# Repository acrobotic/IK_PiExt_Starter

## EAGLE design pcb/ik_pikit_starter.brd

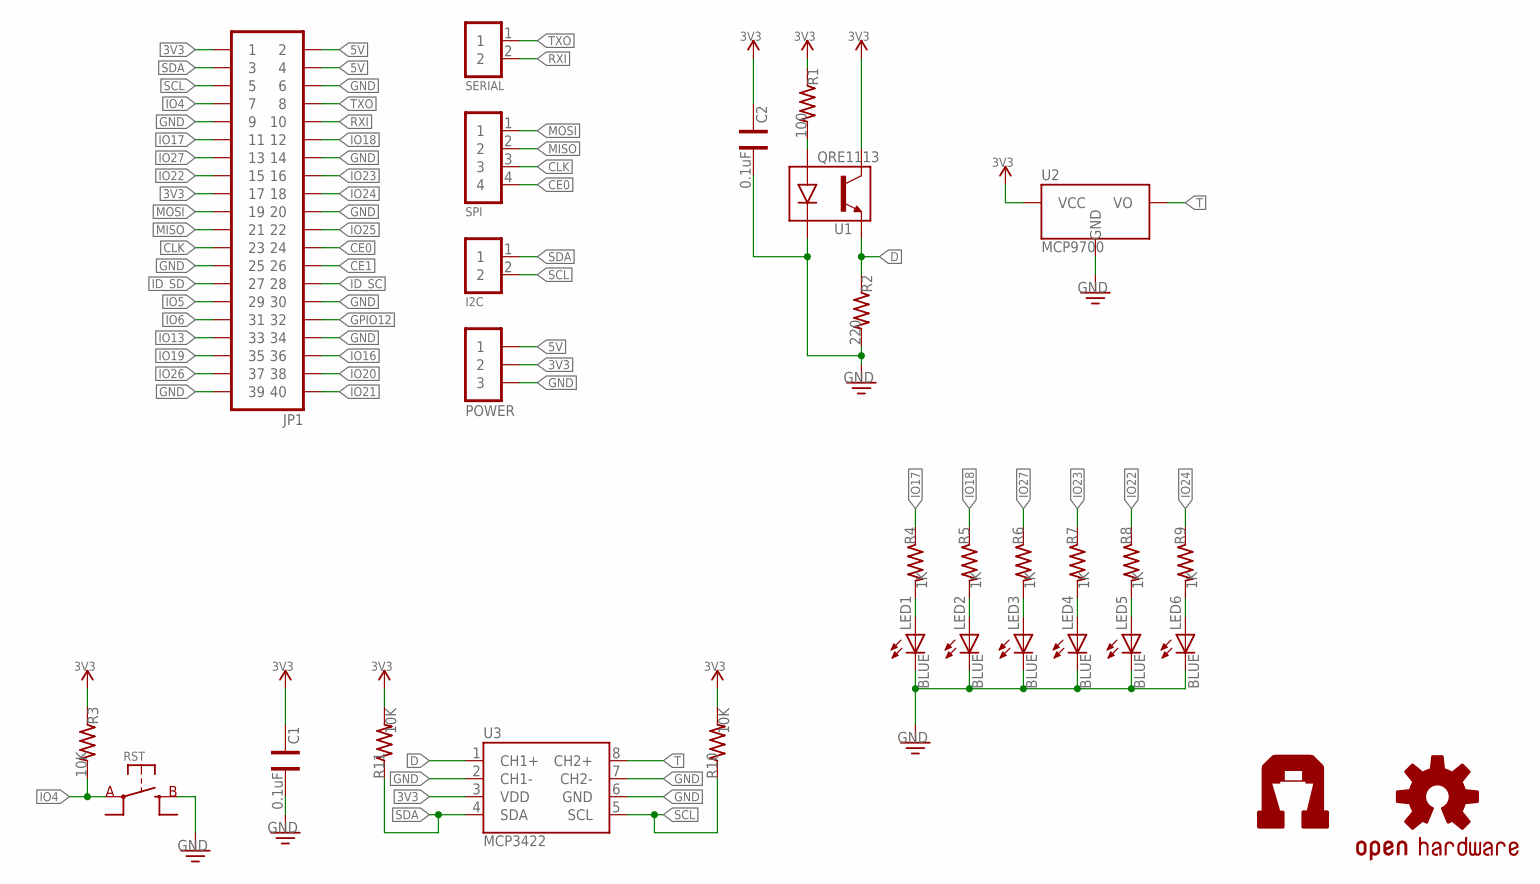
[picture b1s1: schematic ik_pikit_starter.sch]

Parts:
C1, C2: 0.1uF; CAP-0805
I2C: 1X02NOFIRST; 1X02-NOFIRST
JP1: 2X20; 2X20-RPI-BRK
LED1, LED2, LED3, LED4, LED5, LED6: BLUE; LED-0805
LOGO1: OSHW-LOGOS; OSHW-LOGO-S
POWER: 1X03NOFIRST; 1X03-NOFIRST
R1: 100; RES-0805
R2: 220; RES-0805
R3, R10, R11: 10K; RES-0805
R4, R5, R6, R7, R8, R9: 1K; RES-0805
RST: SW-SPSTSMD06X06; SW-SPST-SMD06X06
SERIAL: 1X02NOFIRST; 1X02-NOFIRST
SPI: 1X04NOFIRST; 1X04-NOFIRST
U1: QRE1113
U2: MCP9700SMD; SOT23-3
U3: MCP3422; SO08
U$3: AI-LOGOXS; AI-LOGO-XS

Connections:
3V3: C1.2, C2.2, JP1.1, JP1.17, POWER.2, R1.1, R3.1, R10.2, R11.2, U1.3 (CO), U2.1 (VCC), U3.3 (VDD)
5V: JP1.2, JP1.4, POWER.1
CE0: JP1.24, SPI.4
CE1: JP1.26
CLK: JP1.23, SPI.3
D: R2.1, U1.4 (E), U3.1 (CH1+)
GND: C1.1, C2.1, JP1.6, JP1.9, JP1.14, JP1.20, JP1.25, JP1.30, JP1.34, JP1.39, LED1.C, LED2.C, LED3.C, LED4.C, LED5.C, LED6.C, POWER.3, R2.2, RST.B@1 (B), RST.B@2 (B), U1.2 (CA), U2.3 (GND), U3.2 (CH1-), U3.6 (GND), U3.7 (CH2-)
GPIO12: JP1.32
ID_SC: JP1.28
ID_SD: JP1.27
IO4: JP1.7, R3.2, RST.A@1 (A), RST.A@2 (A)
IO5: JP1.29
IO6: JP1.31
IO13: JP1.33
IO16: JP1.36
IO17: JP1.11, R4.1
IO18: JP1.12, R5.1
IO19: JP1.35
IO20: JP1.38
IO21: JP1.40
IO22: JP1.15, R8.1
IO23: JP1.16, R7.1
IO24: JP1.18, R9.1
IO25: JP1.22
IO26: JP1.37
IO27: JP1.13, R6.1
MISO: JP1.21, SPI.2
MOSI: JP1.19, SPI.1
unnamed: R1.2, U1.1 (A)
unnamed: LED5.A, R8.2
unnamed: LED1.A, R4.2
unnamed: LED2.A, R5.2
unnamed: LED3.A, R6.2
unnamed: LED4.A, R7.2
unnamed: LED6.A, R9.2
RXI: JP1.10, SERIAL.2
SCL: I2C.2, JP1.5, R10.1, U3.5 (SCL)
SDA: I2C.1, JP1.3, R11.1, U3.4 (SDA)
T: U2.2 (VO), U3.8 (CH2+)
TXO: JP1.8, SERIAL.1

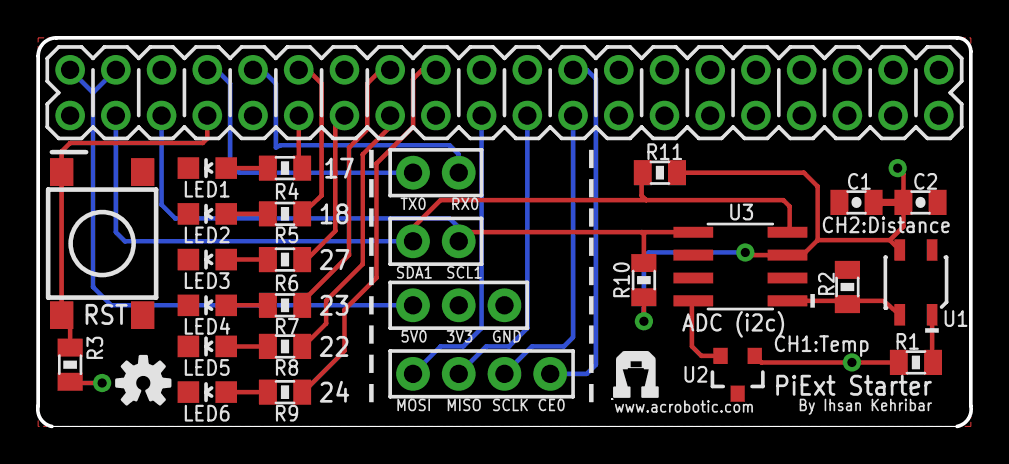
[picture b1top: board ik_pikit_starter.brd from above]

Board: 2 copper layers, 51.8 x 21.6 mm, 30 parts (0 on the bottom side), 27 nets.

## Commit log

2014-08-25 revised version
2014-08-25 removing temp files
2014-08-26 minor revision
2014-09-04 adding values
2014-09-04 fixed silkscreen
2014-09-05 updated BOM
